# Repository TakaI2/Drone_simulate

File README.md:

# Drone Design Studio

固定ピッチの多ロータ機（ドローン）を、飛行シミュレーション → 推進系・電気設計 → 基板の自動配置配線 → 機体設計 → 統合検証まで一貫して設計するツールです。ブラウザだけで動きます。

- 屋内（オプティカルフロー）・屋外（GNSS、風、自動帰還）・都市（横浜みなとみらい、PLATEAU の建物）の飛行シミュレーション
- 推進系の探索、回路生成と電気計算、2 層基板の自動配置・配線、Gerber / KiCad 出力
- 3D プリント用フレームの生成（重心・強度・隙間の検証、STL 出力）
- 3 つの設計例（版 A：1S ブラシ付き、版 B：センサ子基板＋GNSS 端子、版 C：屋外用ブラシレス）と予算

使い方は [docs/manual.md](docs/manual.md)、設計の経緯と検証結果は `reports/index.html` を参照してください。

## 開発

```bash
npm install
npm run dev        # http://localhost:5173
npm test
npm run build      # dist/ にサイト一式（アプリ＋out/・reports/・docs/、マニュアルの HTML 版）
```

## 公開（Netlify）

`netlify.toml` に設定済みです（ビルド `npm run build`、公開ディレクトリ `dist`）。Netlify で GitHub リポジトリを連携すると、push のたびに自動で公開されます。設計データ（`out/`）とレポートはリポジトリに含めたものを公開するので、設計を変えたら各スクリプト（`npm run all` など）を実行してから push してください。

## 注意

結果はシミュレーションと計算上の値で、実機の安全性・性能・飛行の可否を保証しません。飛行は法令・条例に従ってください（詳しくは `notice.html`）。

## ライセンス

ソースコードは [MIT License](LICENSE)。データ（PLATEAU、OpenStreetMap など）とライブラリのライセンスは [THIRD_PARTY_NOTICES.md](THIRD_PARTY_NOTICES.md) を参照してください（`out/city/buildings_osm.json` は ODbL 1.0）。

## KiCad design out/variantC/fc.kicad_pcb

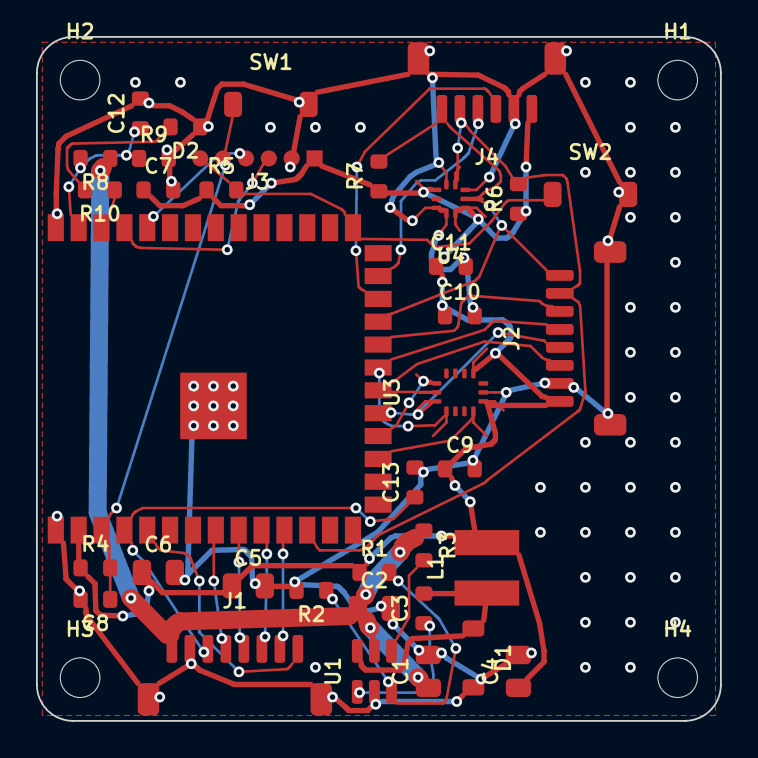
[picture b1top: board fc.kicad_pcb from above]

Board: 2 copper layers, 38.0 x 38.0 mm, 40 parts (0 on the bottom side), 30 nets.

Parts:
C1, C2, C4, C5, C6: 10 µF; C0805
C3, C7, C9, C10, C11, C12, C13: 100 nF; C0603
C8: 1 µF; C0603
D1: B5819W; SOD-123
D2: APT1608EC; LED0603
H1, H2, H3, H4: —; MountHole-M2
J1, J2: SM08B-SRSS-TB(LF)(SN); JST-SH-8-SMD
J3: —; TestPad-1x6-1.27
J4: SM06B-SRSS-TB(LF)(SN); JST-SH-6-SMD
L1: 10 µH; L-Power-4x4
R1, R3, R8: 100kΩ; R0603
R2: 33kΩ; R0603
R4, R5, R9: 10kΩ; R0603
R6, R7: 4.7kΩ; R0603
R10: 1kΩ; R0603
SW1, SW2: TS-1187A-B-A-B; Tact-3x4-SMD
U1: MP2359DJ-LF-Z; SOT-23-6
U2: ESP32-S3-WROOM-1-N8; ESP32-S3-WROOM-1
U3: ICM-42688-P; LGA-14-2.5x3
U4: BMP390; LGA-10-2x2

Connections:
3V3: C4.1, C5.1, C6.1, C7.1, C9.1, C10.1, C11.1, J2.1, J3.1, J4.1, L1.2, R1.1, R4.1, R5.1, R6.1, R7.1, U2.2, U3.5, U3.8, U4.1, U4.6, U4.10
BOOT: J3.6, R5.2, SW2.1, U2.27
BST: C3.1, U1.1
BUCK_EN: R3.2, U1.4
EN: C8.1, J3.5, R4.2, SW1.1, U2.3
ESC_CURR: C13.1, J1.3, U2.4
ESC_M1: J1.4, U2.8
ESC_M2: J1.5, U2.9
ESC_M3: J1.6, U2.10
ESC_M4: J1.7, U2.11
ESC_TLM: J1.8, U2.5
FB: R1.2, R2.1, U1.3
FLOW_CS: J2.6, U2.22
GND: C1.2, C2.2, C4.2, C5.2, C6.2, C7.2, C8.2, C9.2, C10.2, C11.2, C12.2, C13.2, D1.2, D2.1, J1.2, J1.MP1, J1.MP2, J2.2, J2.MP1, J2.MP2, J3.2, J4.2, J4.MP1, J4.MP2, R2.2, R9.2, SW1.2, SW2.2, U1.2, U2.1, U2.40, U2.41, U3.6, U4.3, U4.5, U4.8, U4.9
GNSS_RX: J4.4, U2.25
GNSS_TX: J4.3, U2.24
I2C_SCL: J2.8, J4.6, R7.2, U2.23, U4.2
I2C_SDA: J2.7, J4.5, R6.2, U2.12, U4.4
IMU_CS: U2.18, U3.12
IMU_INT: U2.17, U3.4
LED: R10.1, U2.38
LED_A: D2.2, R10.2
RXD0: J3.4, U2.36
SPI_MISO: J2.5, U2.21, U3.1
SPI_MOSI: J2.4, U2.19, U3.14
SPI_SCK: J2.3, U2.20, U3.13
SW: C3.2, D1.1, L1.1, U1.6
TXD0: J3.3, U2.37
VBAT: C1.1, C2.1, J1.1, R3.1, R8.1, U1.5
VBAT_SENSE: C12.1, R8.2, R9.1, U2.39

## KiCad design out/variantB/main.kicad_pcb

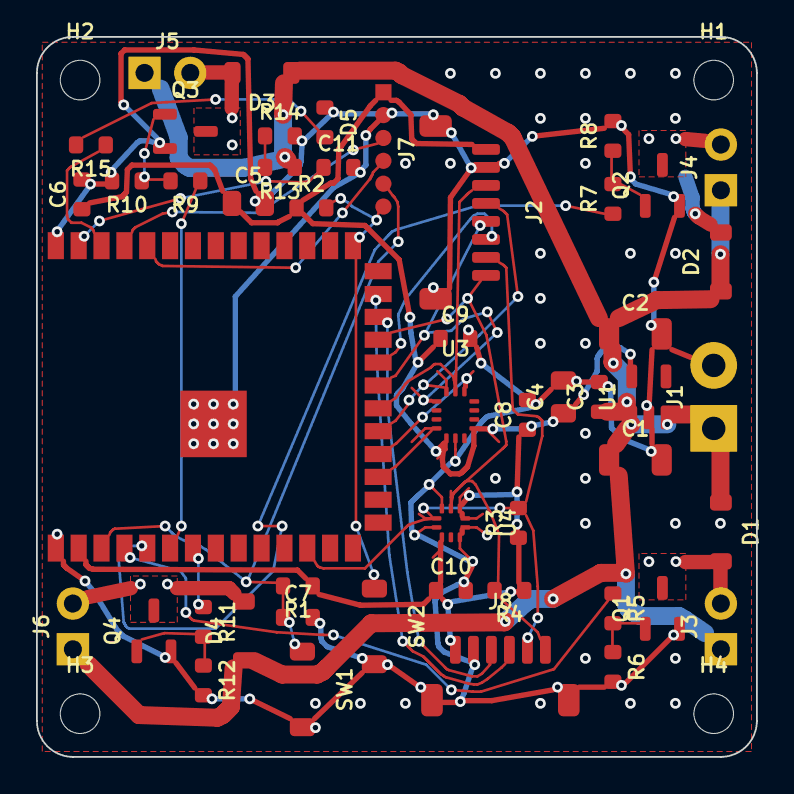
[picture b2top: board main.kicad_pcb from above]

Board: 2 copper layers, 40.0 x 40.0 mm, 53 parts (0 on the bottom side), 32 nets.

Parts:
C1, C2: 47 µF; C1206
C3, C7: 1 µF; C0603
C4, C5: 10 µF; C0805
C6, C8, C9, C10, C11: 100 nF; C0603
D1, D2, D3, D4: B5819W; SOD-123
D5: APT1608EC; LED0603
H1, H2, H3, H4: —; MountHole-M2
J1: —; BatteryPad-2
J2: SM08B-SRSS-TB(LF)(SN); JST-SH-8-SMD
J3, J4, J5, J6: —; MotorPad-2
J7: —; TestPad-1x6-1.27
J8: SM06B-SRSS-TB(LF)(SN); JST-SH-6-SMD
Q1, Q2, Q3, Q4: AO3400A; SOT-23
R1, R2, R6, R8, R10, R12: 10kΩ; R0603
R3, R4: 4.7kΩ; R0603
R5, R7, R9, R11: 47Ω; R0603
R13, R14: 100kΩ; R0603
R15: 1kΩ; R0603
SW1, SW2: TS-1187A-B-A-B; Tact-3x4-SMD
U1: XC6220B331MR-G; SOT-23-5
U2: ESP32-S3-WROOM-1-N8; ESP32-S3-WROOM-1
U3: ICM-42688-P; LGA-14-2.5x3
U4: BMP390; LGA-10-2x2

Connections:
3V3: C4.1, C5.1, C6.1, C8.1, C9.1, C10.1, J2.1, J7.1, J8.1, R1.1, R2.1, R3.1, R4.1, U1.5, U2.2, U3.5, U3.8, U4.1, U4.6, U4.10
BOOT: J7.6, R2.2, SW2.1, U2.27
EN: C7.1, J7.5, R1.2, SW1.1, U2.3
FLOW_CS: J2.6, U2.22
GATE1: Q1.1, R5.2, R6.1
GATE2: Q2.1, R7.2, R8.1
GATE3: Q3.1, R9.2, R10.1
GATE4: Q4.1, R11.2, R12.1
GND: C1.2, C2.2, C3.2, C4.2, C5.2, C6.2, C7.2, C8.2, C9.2, C10.2, C11.2, D5.1, J1.2, J2.2, J2.MP1, J2.MP2, J7.2, J8.2, J8.MP1, J8.MP2, Q1.2, Q2.2, Q3.2, Q4.2, R6.2, R8.2, R10.2, R12.2, R14.2, SW1.2, SW2.2, U1.2, U2.1, U2.40, U2.41, U3.6, U4.3, U4.5, U4.8, U4.9
GNSS_RX: J8.4, U2.25
GNSS_TX: J8.3, U2.24
I2C_SCL: J2.8, J8.6, R4.2, U2.23, U4.2
I2C_SDA: J2.7, J8.5, R3.2, U2.12, U4.4
IMU_CS: U2.18, U3.12
IMU_INT: U2.17, U3.4
LED: R15.1, U2.38
LED_A: D5.2, R15.2
MOT1-: D1.2, J3.2, Q1.3
MOT2-: D2.2, J4.2, Q2.3
MOT3-: D3.2, J5.2, Q3.3
MOT4-: D4.2, J6.2, Q4.3
PWM1: R5.1, U2.4
PWM2: R7.1, U2.5
PWM3: R9.1, U2.6
PWM4: R11.1, U2.7
RXD0: J7.4, U2.36
SPI_MISO: J2.5, U2.21, U3.1
SPI_MOSI: J2.4, U2.19, U3.14
SPI_SCK: J2.3, U2.20, U3.13
TXD0: J7.3, U2.37
VBAT: C1.1, C2.1, C3.1, D1.1, D2.1, D3.1, D4.1, J1.1, J3.1, J4.1, J5.1, J6.1, R13.1, U1.1, U1.3
VBAT_SENSE: C11.1, R13.2, R14.1, U2.39

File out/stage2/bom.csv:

Refs,Qty,Name,Value,MPN,Manufacturer,Package,UnitMass_g,Alternatives,Verify,Search
C1 C2,2,積層セラミックコンデンサ 47 µF 6.3 V X5R 1206,47 µF,GRM31CR60J476ME19L,Murata,C1206,0.03,Samsung Electro-Mechanics CL シリーズ同等品 / TDK C シリーズ同等品,,https://www.digikey.jp/ja/products/result?keywords=GRM31CR60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
C3 C7,2,積層セラミックコンデンサ 1 µF 10 V X5R 0603,1 µF,GRM188R61A105KA61D,Murata,C0603,0.005,Samsung Electro-Mechanics CL シリーズ同等品 / TDK C シリーズ同等品,,https://www.digikey.jp/ja/products/result?keywords=GRM188R61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
C4 C5,2,積層セラミックコンデンサ 10 µF 10 V X5R 0805,10 µF,GRM21BR61A106KE19L,Murata,C0805,0.012,Samsung Electro-Mechanics CL シリーズ同等品 / TDK C シリーズ同等品,,https://www.digikey.jp/ja/products/result?keywords=GRM21BR61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
C6 C8 C9 C10 C11,5,積層セラミックコンデンサ 100 nF 16 V X7R 0603,100 nF,GRM188R71C104KA01D,Murata,C0603,0.005,Samsung Electro-Mechanics CL シリーズ同等品 / TDK C シリーズ同等品,,https://www.digikey.jp/ja/products/result?keywords=GRM188R71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
D1 D2 D3 D4,4,ショットキーダイオード 40 V 1 A（モータ還流用）,B5819W,B5819W,各社（汎用品）,SOD-123,0.01,各社 SS14 / onsemi MBR0540,,https://www.digikey.jp/ja/products/result?keywords=B5819W
D5,1,チップ LED 赤 0603(1608),APT1608EC,APT1608EC,Kingbright,LED0603,0.003,ROHM SML-D12U1W,,https://www.digikey.jp/ja/products/result?keywords=APT1608EC
H1 H2 H3 H4,4,M2 取付穴,—,—,—,MountHole-M2,0,,,
J1,1,電池リード直付けパッド（2 極、20 AWG 用）,—,—,—,BatteryPad-2,0,J.S.T. Mfg. B2B-PH-K-S,,
J2,1,フロー＋ToF モジュール用 JST SH 8 ピン（SMD）,SM08B-SRSS-TB(LF)(SN),SM08B-SRSS-TB(LF)(SN),J.S.T. Mfg.,JST-SH-8-SMD,0.1,各社 SH 互換 1.0 mm 8P,,https://www.digikey.jp/ja/products/result?keywords=SM08B-SRS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
J3 J4 J5 J6,4,モータ配線用スルーホールパッド（2 極）,—,—,—,MotorPad-2,0,,,
J7,1,書込み用テストパッド 1×6（1.27 mm、ポゴピン治具で接触）,—,—,—,TestPad-1x6-1.27,0,各社 2.54 mm ピンヘッダ 1×6,,
Q1 Q2 Q3 Q4,4,N-ch MOSFET 30 V 5.7 A（ロジックレベル）,AO3400A,AO3400A,Alpha & Omega Semiconductor,SOT-23,0.008,Vishay SI2302CDS / Diodes Inc. DMG3420U,,https://www.digikey.jp/ja/products/result?keywords=AO3400A
R1 R2 R6 R8 R10 R12,6,チップ抵抗 10kΩ 1% 0603(1608),10kΩ,RC0603FR-0710KL,Yageo,R0603,0.002,Panasonic ERJ-3EKF10KV 相当 / KOA RK73H1JTTD 相当,,https://www.digikey.jp/ja/products/result?keywords=RC0603FR-0710KL
R3 R4,2,チップ抵抗 4.7kΩ 1% 0603(1608),4.7kΩ,RC0603FR-074K7L,Yageo,R0603,0.002,Panasonic ERJ-3EKF4K7V 相当 / KOA RK73H1JTTD 相当,,https://www.digikey.jp/ja/products/result?keywords=RC0603FR-074K7L
R5 R7 R9 R11,4,チップ抵抗 47Ω 1% 0603(1608),47Ω,RC0603FR-0747RL,Yageo,R0603,0.002,Panasonic ERJ-3EKF47RV 相当 / KOA RK73H1JTTD 相当,,https://www.digikey.jp/ja/products/result?keywords=RC0603FR-0747RL
R13 R14,2,チップ抵抗 100kΩ 1% 0603(1608),100kΩ,RC0603FR-07100KL,Yageo,R0603,0.002,Panasonic ERJ-3EKF100KV 相当 / KOA RK73H1JTTD 相当,,https://www.digikey.jp/ja/products/result?keywords=RC0603FR-07100KL
R15,1,チップ抵抗 1kΩ 1% 0603(1608),1kΩ,RC0603FR-071KL,Yageo,R0603,0.002,Panasonic ERJ-3EKF1KV 相当 / KOA RK73H1JTTD 相当,,https://www.digikey.jp/ja/products/result?keywords=RC0603FR-071KL
SW1 SW2,2,タクトスイッチ 3×4 mm（SMD）,TS-1187A-B-A-B,TS-1187A-B-A-B,XKB Connection,Tact-3x4-SMD,0.05,Alps Alpine SKRPACE010,,https://www.digikey.jp/ja/products/result?keywords=TS-1187A-B-A-B
U1,1,3.3 V LDO レギュレータ 1 A,XC6220B331MR-G,XC6220B331MR-G,Torex,SOT-23-5,0.015,Diodes Inc. AP2112K-3.3TRG1 / Microne ME6211C33M5G,SOT-25 のピン配置（VIN/VSS/CE/NC/VOUT）,https://www.digikey.jp/ja/products/result?keywords=XC6220B331MR-G
U2,1,"Wi-Fi/BLE マイコンモジュール ESP32-S3（8MB Flash, PSRAM なし）",ESP32-S3-WROOM-1-N8,ESP32-S3-WROOM-1-N8,Espressif Systems,ESP32-S3-WROOM-1,3,Espressif Systems ESP32-S3-MINI-1-N8 / M5Stack M5Stamp S3 / STMicroelectronics STM32F405 + 外付け無線,モジュール寸法とパッド位置（1.27 mm ピッチ）、アンテナ禁止領域,https://www.digikey.jp/ja/products/result?keywords=ESP32-S3-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
U3,1,6軸 IMU（ジャイロ＋加速度）,ICM-42688-P,ICM-42688-P,TDK InvenSense,LGA-14-2.5x3,0.02,Bosch Sensortec BMI270 / STMicroelectronics LSM6DSO,ピン番号と RESV ピンの処理、推奨デカップリング容量,https://www.digikey.jp/ja/products/result?keywords=ICM-42688-P
U4,1,気圧センサ,BMP390,BMP390,Bosch Sensortec,LGA-10-2x2,0.01,Infineon DPS310 / STMicroelectronics LPS22HB,ピン配置と通気穴の向き,https://www.digikey.jp/ja/products/result?keywords=BMP390

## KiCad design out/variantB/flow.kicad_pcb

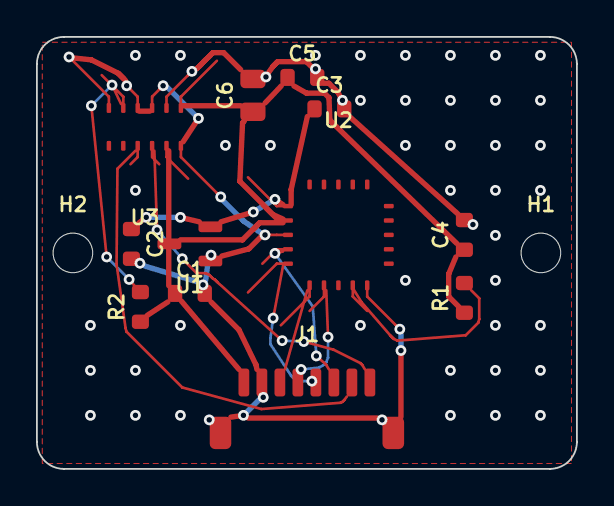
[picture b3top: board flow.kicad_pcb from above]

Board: 2 copper layers, 30.0 x 24.0 mm, 14 parts (0 on the bottom side), 11 nets.

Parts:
C1, C2: 1 µF; C0603
C3, C4, C5: 100 nF; C0603
C6: 10 µF; C0805
H1, H2: —; MountHole-M2
J1: SM08B-SRSS-TB(LF)(SN); JST-SH-8-SMD
R1, R2: 10kΩ; R0603
U1: XC6206P182MR-G; SOT-23
U2: PMW3901MB-TXQT; PMW3901MB
U3: VL53L1CXV0FY/1; VL53L1X-LGA12

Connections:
1V8: C2.1, C3.1, U1.2, U2.1
3V3: C1.1, C4.1, C5.1, C6.1, J1.1, R1.1, R2.1, U1.3, U2.2, U3.1, U3.11
FLOW_CS: J1.6, U2.4
FLOW_NRST: R1.2, U2.9
GND: C1.2, C2.2, C3.2, C4.2, C5.2, C6.2, J1.2, J1.MP1, J1.MP2, U1.1, U2.3, U2.10, U3.2, U3.3, U3.4, U3.6, U3.12
I2C_SCL: J1.8, U3.10
I2C_SDA: J1.7, U3.9
SPI_MISO: J1.5, U2.5
SPI_MOSI: J1.4, U2.7
SPI_SCK: J1.3, U2.6
TOF_XSHUT: R2.2, U3.5
